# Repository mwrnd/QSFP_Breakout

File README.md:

**Work-In-Progress**: Design being tested. A second revision will be needed as the QSFP Cage Mounting pads are incorrect.

# QSFP Breakout

[QSFP](https://en.wikipedia.org/wiki/Small_Form-factor_Pluggable#QSFP) to [U.FL/UMCC Connector](https://en.wikipedia.org/wiki/Hirose_U.FL) breakout.

Additional I2C circuitry is due to this being a stepping stone project for an [OpenCAPI](https://files.openpower.foundation/s/xSQPe6ypoakKQdq/download/25Gbps-spec-20171108.pdf) to **dual** QSFP design. OpenCAPI has only a single I2C interface.

# PCB Layout

All differential signals are length-matched to within 1mm of a 25mm total length, both inter-pair and intra-pair.

# Schematic

# PCB Layer Stackup

4-Layer PCB stackup taken from [JLCPCB](https://jlcpcb.com/capabilities/pcb-capabilities).

100-ohm Differential Impedance parameters were calculated using the [DigiKey Online Calculator](https://www.digikey.com/en/resources/conversion-calculators/conversion-calculator-pcb-trace-impedance).

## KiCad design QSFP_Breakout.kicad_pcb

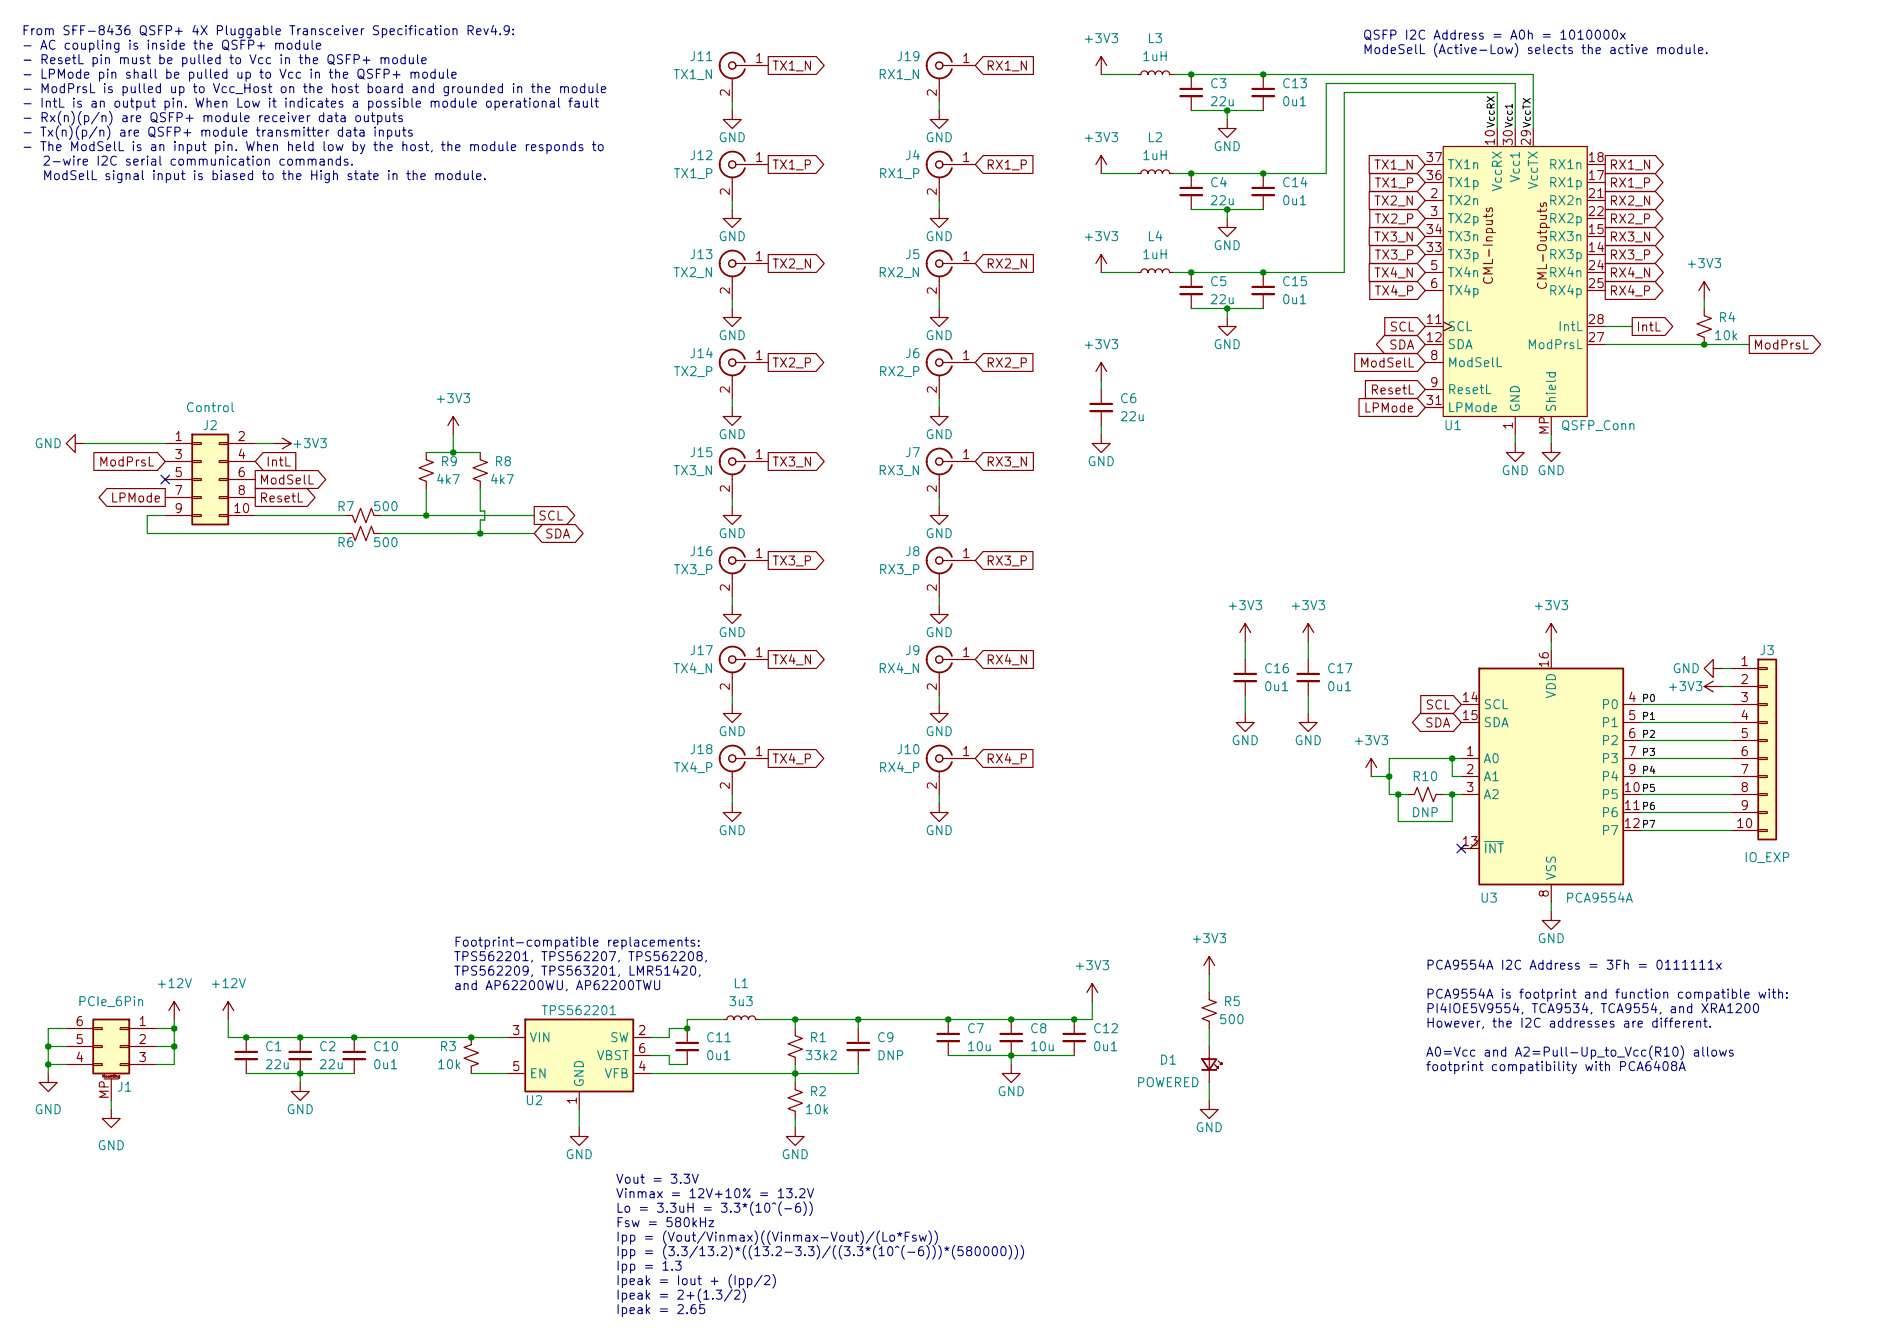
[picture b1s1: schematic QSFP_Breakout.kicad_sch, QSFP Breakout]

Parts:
C1, C2, C3, C4, C5, C6: 22u; C_0805_2012Metric_Pad1.18x1.45mm_HandSolder
C7, C8: 10u; C_0805_2012Metric_Pad1.18x1.45mm_HandSolder
C9: DNP; C_0603_1608Metric_Pad1.08x0.95mm_HandSolder
C10, C11, C12, C13, C14, C15, C16, C17: 0u1; C_0603_1608Metric_Pad1.08x0.95mm_HandSolder
D1: POWERED; D_0603_1608Metric_Pad1.05x0.95mm_HandSolder
J1: PCIe_6Pin; ATX_PCIe_6-Pin_Power_Board-Edge
J2: Control; PinSocket_2x05_P2.54mm_Vertical
J3: IO_EXP; PinSocket_2x05_P2.54mm_Vertical
J4: RX1_P; U.FL_Hirose_w_Label
J5: RX2_N; U.FL_Hirose_w_Label
J6: RX2_P; U.FL_Hirose_w_Label
J7: RX3_N; U.FL_Hirose_w_Label
J8: RX3_P; U.FL_Hirose_w_Label
J9: RX4_N; U.FL_Hirose_w_Label
J10: RX4_P; U.FL_Hirose_w_Label
J11: TX1_N; U.FL_Hirose_w_Label
J12: TX1_P; U.FL_Hirose_w_Label
J13: TX2_N; U.FL_Hirose_w_Label
J14: TX2_P; U.FL_Hirose_w_Label
J15: TX3_N; U.FL_Hirose_w_Label
J16: TX3_P; U.FL_Hirose_w_Label
J17: TX4_N; U.FL_Hirose_w_Label
J18: TX4_P; U.FL_Hirose_w_Label
J19: RX1_N; U.FL_Hirose_w_Label
L1: 3u3; L_Bourns-SRN8040_8x8.15mm
L2, L3, L4: 1uH; L_0805_2012Metric_Pad1.15x1.40mm_HandSolder
R1: 33k2; R_0603_1608Metric_Pad0.98x0.95mm_HandSolder
R2, R3, R4: 10k; R_0603_1608Metric_Pad0.98x0.95mm_HandSolder
R5, R6, R7: 500; R_0603_1608Metric_Pad0.98x0.95mm_HandSolder
R8, R9: 4k7; R_0603_1608Metric_Pad0.98x0.95mm_HandSolder
R10: DNP; R_0603_1608Metric_Pad0.98x0.95mm_HandSolder
U1: QSFP_Conn; QSFP_Conn_w_Cage
U2: TPS562201; SOT-23-6
U3: PCA9554A; TSSOP-16_4.4x5mm_P0.65mm

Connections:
+3V3: C6.1, C7.1, C8.1, C9.1, C12.1, C16.1, C17.1, J2.2, J3.2, L1.2, L2.1, L3.1, L4.1, R1.1, R4.1, R5.1, R8.1, R9.1, R10.1, R10.2, U3.1 (A0), U3.2 (A1), U3.3 (A2), U3.16 (VDD)
+12V: C1.1, C2.1, C10.1, J1.1, J1.2, J1.3, R3.1, U2.3 (VIN)
/P0: J3.3, U3.4 (P0)
/P1: J3.4, U3.5 (P1)
/P2: J3.5, U3.6 (P2)
/P3: J3.6, U3.7 (P3)
/P4: J3.7, U3.9 (P4)
/P5: J3.8, U3.10 (P5)
/P6: J3.9, U3.11 (P6)
/P7: J3.10, U3.12 (P7)
/Vcc1: C4.1, C14.1, L2.2, U1.30 (Vcc1)
/VccRX: C5.1, C15.1, L4.2, U1.10 (VccRX)
/VccTX: C3.1, C13.1, L3.2, U1.29 (VccTX)
GND: C1.2, C2.2, C3.2, C4.2, C5.2, C6.2, C7.2, C8.2, C10.2, C12.2, C13.2, C14.2, C15.2, C16.2, C17.2, D1.1 (K), J1.4, J1.5, J1.6, J1.MP (MountPin), J2.1, J3.1, J4.2 (Ext), J5.2 (Ext), J6.2 (Ext), J7.2 (Ext), J8.2 (Ext), J9.2 (Ext), J10.2 (Ext), J11.2 (Ext), J12.2 (Ext), J13.2 (Ext), J14.2 (Ext), J15.2 (Ext), J16.2 (Ext), J17.2 (Ext), J18.2 (Ext), J19.2 (Ext), R2.2, U1.1 (GND), U1.4 (GND), U1.7 (GND), U1.13 (GND), U1.16 (GND), U1.19 (GND), U1.20 (GND), U1.23 (GND), U1.26 (GND), U1.32 (GND), U1.35 (GND), U1.38 (GND), U1.MP (Shield), U2.1 (GND), U3.8 (VSS)
IntL: J2.4, U1.28 (IntL)
LPMode: J2.7, U1.31 (LPMode)
ModPrsL: J2.3, R4.2, U1.27 (ModPrsL)
ModSelL: J2.6, U1.8 (ModSelL)
unnamed: D1.2 (A), R5.2
unnamed: J2.9, R6.2
unnamed: J2.10, R7.2
unnamed: R3.2, U2.5 (EN)
unnamed: C11.1, L1.1, U2.2 (SW)
unnamed: C11.2, U2.6 (VBST)
unnamed: C9.2, R1.2, R2.1, U2.4 (VFB)
RX1_N: J19.1 (In), U1.18 (RX1n)
RX1_P: J4.1 (In), U1.17 (RX1p)
RX2_N: J5.1 (In), U1.21 (RX2n)
RX2_P: J6.1 (In), U1.22 (RX2p)
RX3_N: J7.1 (In), U1.15 (RX3n)
RX3_P: J8.1 (In), U1.14 (RX3p)
RX4_N: J9.1 (In), U1.24 (RX4n)
RX4_P: J10.1 (In), U1.25 (RX4p)
ResetL: J2.8, U1.9 (ResetL)
SCL: R7.1, R9.2, U1.11 (SCL), U3.14 (SCL)
SDA: R6.1, R8.2, U1.12 (SDA), U3.15 (SDA)
TX1_N: J11.1 (In), U1.37 (TX1n)
TX1_P: J12.1 (In), U1.36 (TX1p)
TX2_N: J13.1 (In), U1.2 (TX2n)
TX2_P: J14.1 (In), U1.3 (TX2p)
TX3_N: J15.1 (In), U1.34 (TX3n)
TX3_P: J16.1 (In), U1.33 (TX3p)
TX4_N: J17.1 (In), U1.5 (TX4n)
TX4_P: J18.1 (In), U1.6 (TX4p)

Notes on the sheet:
From SFF-8436 QSFP+ 4X Pluggable Transceiver Specification Rev4.9: - AC coupling is inside the QSFP+ module - ResetL pin must be pulled to Vcc in the QSFP+ module - LPMode pin shall be pulled up to Vcc in the QSFP+ module - ModPrsL is pulled up to Vcc_Host on the host board and grounded in the modu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
QSFP I2C Address = A0h = 1010000x ModeSelL (Active-Low) selects the active module.
Vout = 3.3V Vinmax = 12V+10% = 13.2V Lo = 3.3uH = 3.3*(10^(-6)) Fsw = 580kHz Ipp = (Vout/Vinmax)((Vinmax-Vout)/(Lo*Fsw)) Ipp = (3.3/13.2)*((13.2-3.3)/((3.3*(10^(-6)))*(580000))) Ipp = 1.3 Ipeak = Iout + (Ipp/2) Ipeak = 2+(1.3/2) Ipeak = 2.65
PCA9554A I2C Address = 3Fh = 0111111x PCA9554A is footprint and function compatible with: PI4IOE5V9554, TCA9534, TCA9554, and XRA1200 However, the I2C addresses are different. A0=Vcc and A2=Pull-Up_to_Vcc(R10) allows footprint compatibility with PCA6408A
Footprint-compatible replacements: TPS562201, TPS562207, TPS562208, TPS562209, TPS563201, LMR51420, and AP62200WU, AP62200TWU

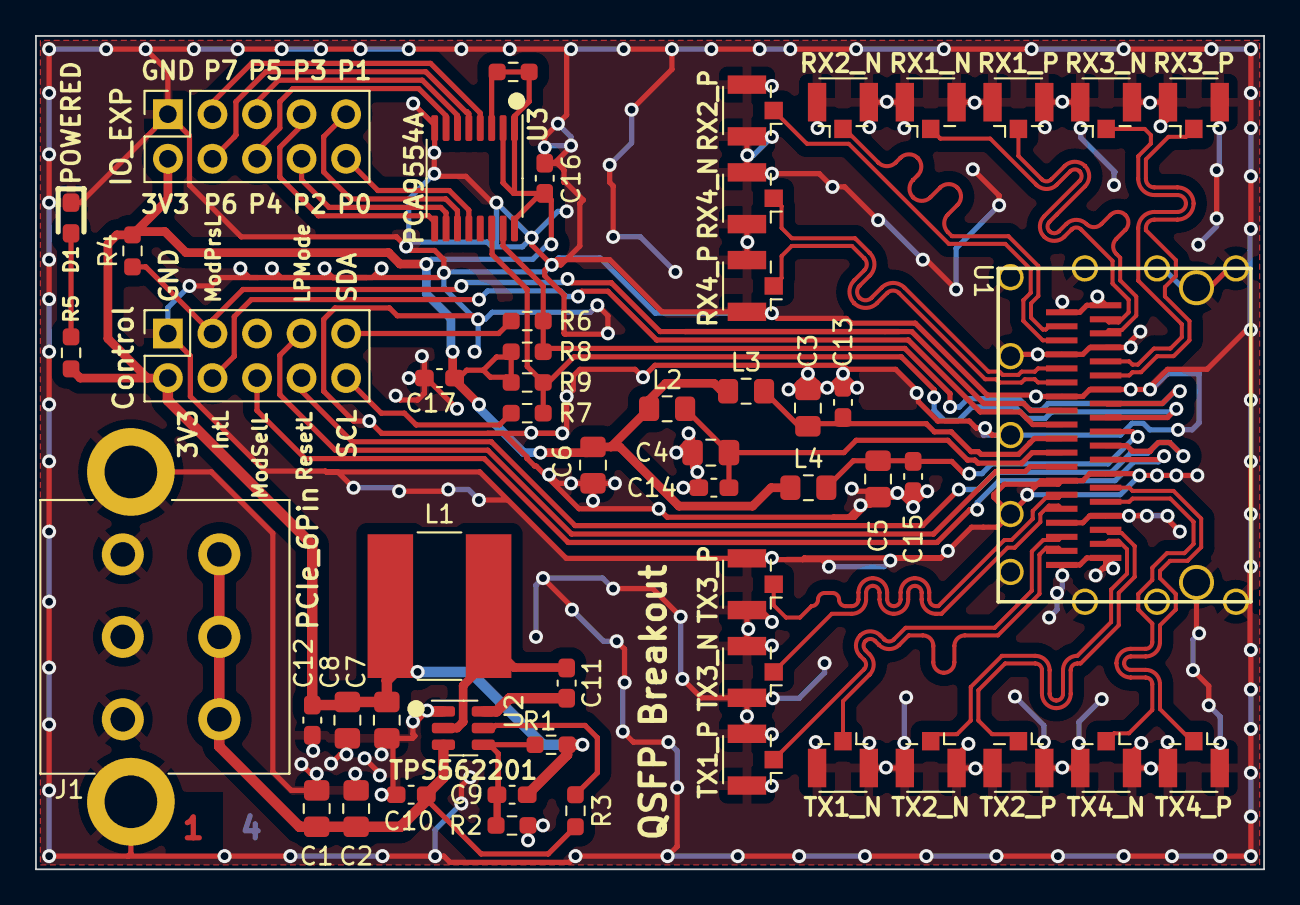
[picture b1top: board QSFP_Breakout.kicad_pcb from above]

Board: 4 copper layers, 70.0 x 47.5 mm, 54 parts (0 on the bottom side), 44 nets.

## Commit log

2023-06-11 First Revision
2023-06-11 README.md Updated
2023-06-12 Updated GND Fill
2023-06-12 v0.1.1 PCB Layout Image
